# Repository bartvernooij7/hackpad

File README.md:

# Hackpad

Hi, this is my Hackpad repository. I originally started making this Hackpad on Blueprint, but Blueprint has ended, so I moved over to Forge to finish.
I designed the macropad for hardware monitoring and functioning as a soundboard. It features an integrated display, a rotary encoder for volume control, and 4 programmable buttons for macros (like passwords) and shortcuts (like `Ctrl+C`). While the screen currently displays a static photo, the software for hardware monitoring and volume control is fully functional.

## what is the purpose of this project 
for my and for other people how to build your own macropad. but why build your own macropad if you can buy one in the store? 
because it is fun to do, and this one is fully customized to my needs and you can customize it to your needs 
## Why Did I Make This?
I built this macropad because I wanted to learn how to design my own PCBs and write custom firmware. This project served as an excellent introduction to creating my first PCB. Additionally, I built it to improve my personal workflow, making it easier to adjust settings and monitor my system while doing homework or 3D modeling.

## How to Assemble
To recreate my Hackpad, you will need a soldering iron, access to a 3D printer, a computer for flashing the firmware, and basic soldering skills.

1. **Order the PCB:** Upload the Gerber files (`macro pad_drl.zip`) found in the `gerbers` folder of my repository to a manufacturer like JLCPCB ([JLCPCB Link](https://shorturl.at/ydwEK)). Order this first, as shipping takes a long time if you want it cheap!
2. **Order Parts:** While waiting for the PCB, order the remaining components from the Bill of Materials (BOM) via AliExpress.
3. **3D Print the Case:** Download the 3D model from the `cadmodel` folder in the repository and print it yourself, or use a site like JLC3DP ([JLC3DP Link](https://jlc3dp.com/3d-printing-quote?from=button)).
4. **Soldering:** Once all parts arrive, solder the components onto the PCB following the reference photos.
5. **Flashing the firmware:** Use the guide below this bullet list to flash the firmware.
6. **Assembly:** Drop the finished PCB into the 3D-printed case. You can use glue for extra security. After that, you can put on the top part of the case and screw it on. 

## Reference pictures for soldering

After you are done with soldering, it should look like this (this is a render). 
If yours looks just like this one, you can put the keycaps on and move on with the next part of making my Hackpad.  

## How to Flash your Hackpad
This project uses an RP2040 microcontroller (a XIAO Seeed).

1. To flash the firmware, I recommend you follow this guide on how to flash microcontrollers for keyboards: [sl1nk.com/z8o8f68](https://sl1nk.com/z8o8f68).
2. Once the firmware is successfully flashed, you can put the PCB in the case, place the top on the case, and secure it with generic screws (or the ones listed in the BOM).

## Bill of Materials (BOM)
Here are all the parts and prices required for this build:

| Item | Price | Link |
| :--- | :--- | :--- |
| Keycaps (Green) | €2.45/$2.86 | [AliExpress Link](https://l1nk.dev/9ejw5r6) |
| Rotary Encoder | €1.52/$1.70 | [AliExpress Link](https://nl.aliexpress.com/item/1005009040530746.html) |
| 128x32 Screen | €1.60/$2.36 | [AliExpress Link](https://nl.aliexpress.com/item/1005013116684555.html?spm=a2g0o.cart.0.0.882661d7mZEAk9&mp=1&pdp_npi=6%40dis%21EUR%21EUR+9.41%21EUR+1.60%21%21EUR+1.60%21%21%21%40210381f017886929285718695e0f68%2112000060258627094%21ct%21NL%214712872211%21%211%210%21&gatewayAdapt=glo2nld) |
| Switches (20pc) | €3.18/$3.71 | [AliExpress Link](https://nl.aliexpress.com/item/1005011838889689.html) |
| Seeed RP2040 | €10.94/$12.77 | [AliExpress Link](https://a.aliexpress.com/_EQkfTBi) |
| Screws | €3.96/$4.59 | [AliExpress Link](https://nl.aliexpress.com/item/1005008724193768.html) |
| PCB | €8.52/$4.26 | N/A |
| Filament | Free (I pay) | N/A |
| **Total AliExpress** | **€23.98/$27.98** | |
| **Total Complete** | **€32.61/$32.25** | |

## Some known Issues (will get fixed)
* The screen currently only displays a static photo; this is because I have not built it yet, so I can't debug it and write software for it.

## Pictures of the Hackpad, schematic, PCB, etc.

## Credits
* Huge thanks to Hack Club and Forge for the support, guides, and help from the community.

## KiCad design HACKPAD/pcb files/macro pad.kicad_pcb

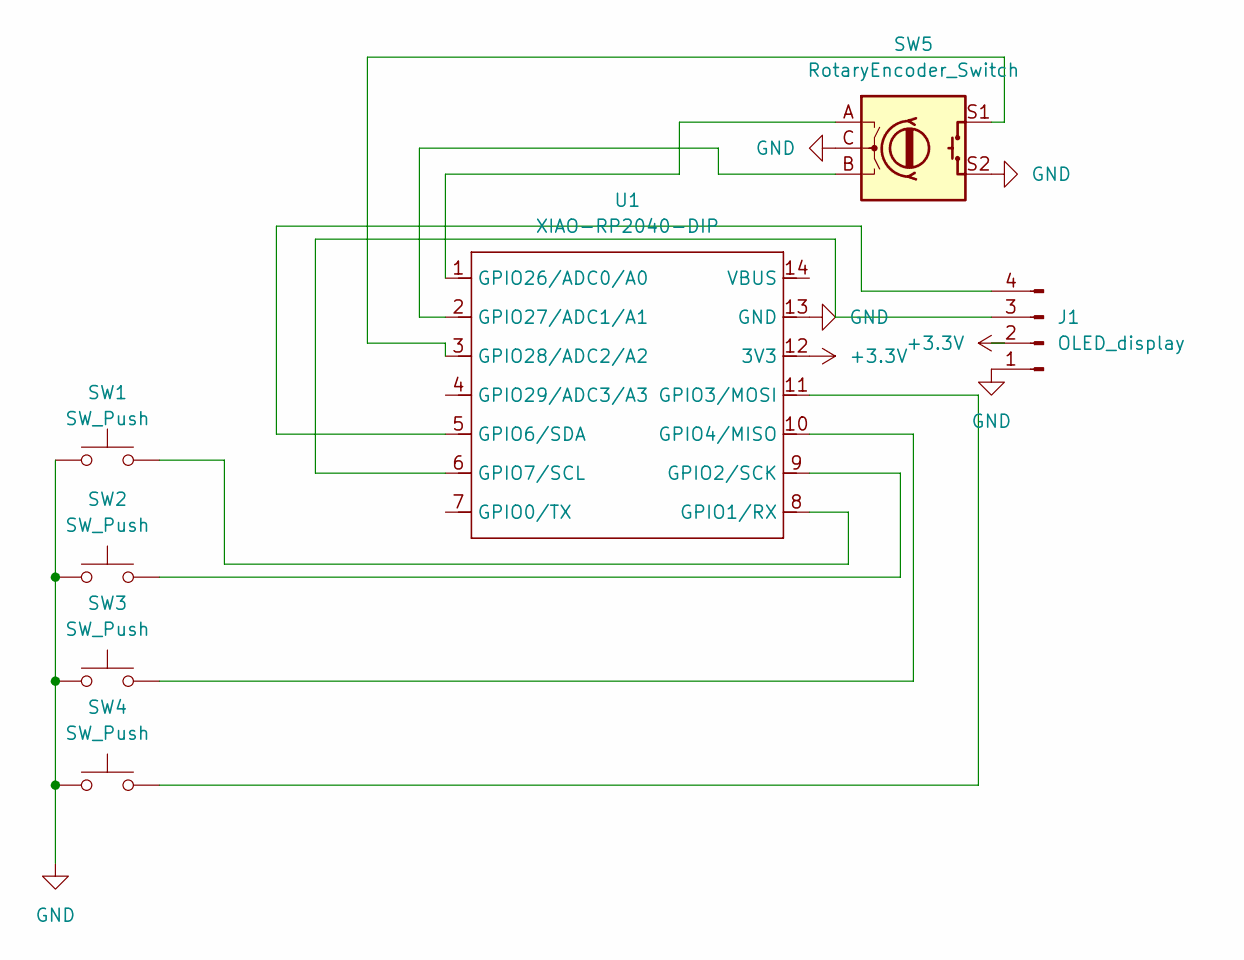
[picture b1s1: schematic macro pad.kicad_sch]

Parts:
J1: OLED_display; PinHeader_1x04_P2.54mm_Horizontal
SW1, SW2, SW3, SW4: SW_Push; SW_Cherry_MX_1.00u_PCB
SW5: RotaryEncoder_Switch; RotaryEncoder_Alps_EC11E-Switch_Vertical_H20mm
U1: XIAO-RP2040-DIP

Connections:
+3.3V: J1.2, U1.12 (3V3)
GND: J1.1, SW1.1, SW2.1, SW3.1, SW4.1, SW5.C, SW5.S2, U1.13 (GND)
unnamed: J1.3, U1.6 (GPIO7/SCL)
unnamed: J1.4, U1.5 (GPIO6/SDA)
unnamed: SW1.2, U1.8 (GPIO1/RX)
unnamed: SW2.2, U1.9 (GPIO2/SCK)
unnamed: SW4.2, U1.11 (GPIO3/MOSI)
unnamed: SW3.2, U1.10 (GPIO4/MISO)
unnamed: SW5.A, U1.1 (GPIO26/ADC0/A0)
unnamed: SW5.B, U1.2 (GPIO27/ADC1/A1)
unnamed: SW5.S1, U1.3 (GPIO28/ADC2/A2)

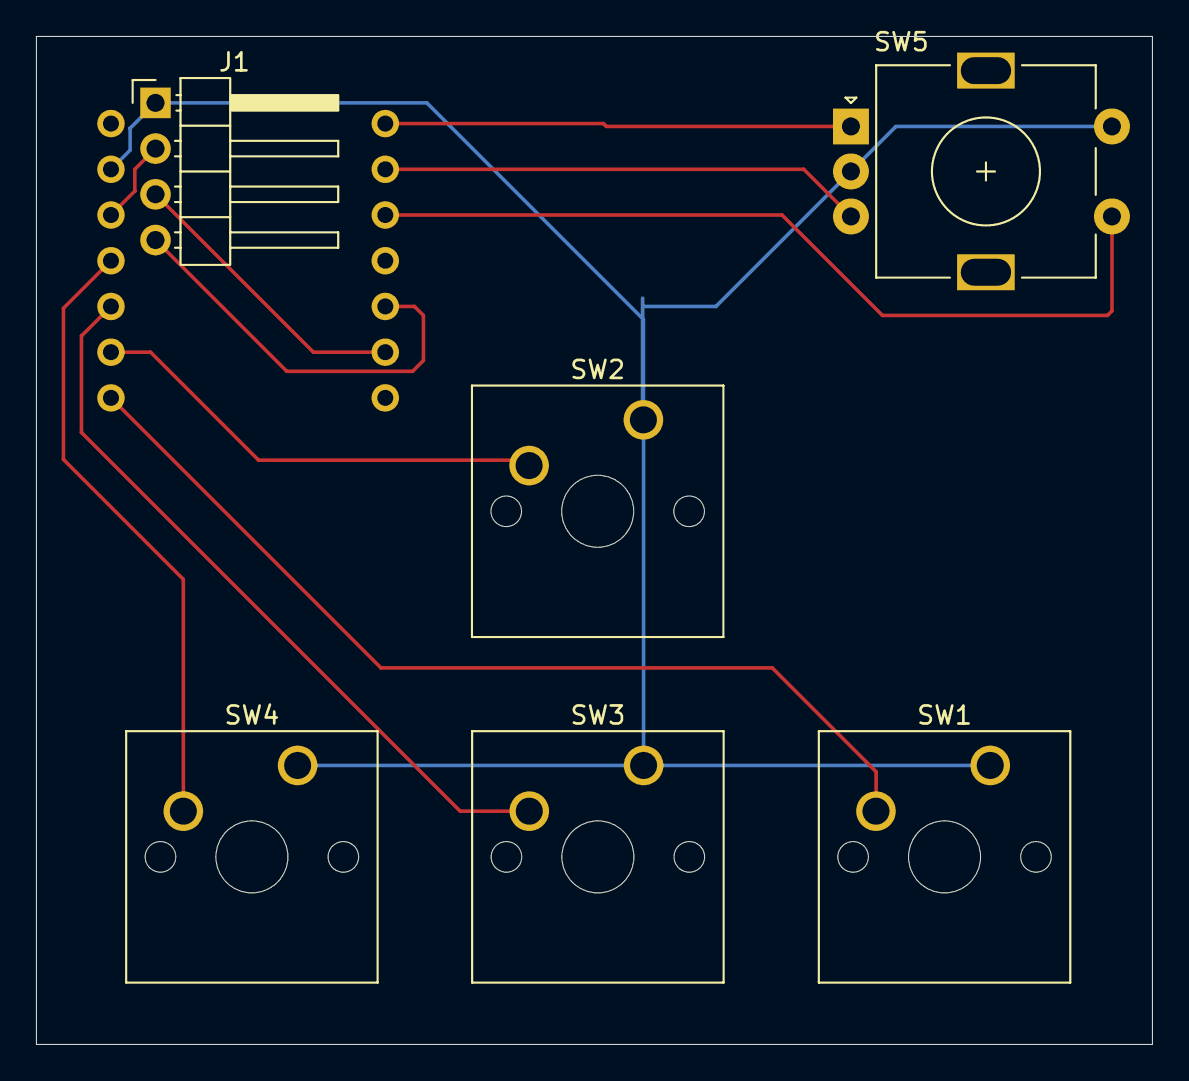
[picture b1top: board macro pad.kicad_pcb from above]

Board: 2 copper layers, 62.0 x 56.0 mm, 7 parts (1 on the bottom side), 11 nets.

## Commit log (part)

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2026-03-31 files upload
2026-04-13 files moved
2026-04-14 .pcb and .pro add
2026-04-14 .sch add
2026-04-14 .drl add
2026-04-14 drl files
2026-04-14 firmware
2026-04-14 bom tabel
2026-04-24 removed old drl files and other
2026-04-24 removed old bom
2026-04-24 bom update
2026-04-25 gerberfiles removed because no workie
2026-04-25 rework
2026-04-25 gerber files rework
2026-04-25 Replace an image in README with a new one
2026-04-25 Update README with corrections and additional images
    Fixed typos and added new images to the README.
2026-04-25 update images in README.md
    Updated images and corrected typos in the README.
2026-06-04 update images in README.md and added a bom to the readme
2026-06-04 reupload
